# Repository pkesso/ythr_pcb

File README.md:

# PCBs — THR pedalboard

Hardware spec for the JLCPCB build of the control surface. The prototype it
replaces is described in the firmware repository (`feather/doc/wiring.md`); pin
assignments and the 7-segment bit order stay as there, so the firmware does not
change.

## Setup

KiCad 10 (`kicad-cli`) and Python 3 with the packages in `requirements.txt`:

```bash
python -m venv .venv
.venv/Scripts/pip install -r requirements.txt
.venv/Scripts/python effect/gen_effect.py                      # one board
.venv/Scripts/python -m unittest discover -s tests -t tests    # all tests
```

How the boards are generated and tested: [common/README.md](common/README.md).

## Boards

| Dir | Board | MCP23017 | Size (max) | Mask colour |
|-----|-------|----------|------------|-------------|
| `main/` | Main: Main 1 + Main 2 + 7-seg + Feather + bus hub | 0x20, 0x21 | 180 × 110 mm | green |
| `gain-compressor/` | Gate + Compressor (Rev0: hot-swap I²C buffer, VCC ferrite, debounced Q27 push buttons on the board, RJ45 with LEDs) | 0x22 | 50 × 104 mm (template Type_Z-76_Z-77) | yellow |
| `effect/` | Effect (Rev0: Q27 push buttons on the board, RJ45 with LEDs, hot-swap I²C buffer, VCC ferrite) | 0x23 | 50 × 104 mm (template Type_Z-76_Z-77) | purple |
| `echo/` | Echo | 0x24 | 50 × 65 mm | white (black silk) |
| `rever/` | Reverb (Rev0: as Effect) | 0x25 | 50 × 104 mm (template Type_Z-76_Z-77) | blue |
| `presets/` | Presets | 0x26 | 200 × 50 mm | black |

Develop (0x27) gets no PCB.

`common/` is not a board: it holds the generator scripts and the shared KiCad libraries
(see [common/README.md](common/README.md)); `tools/` holds the KiCad helper scripts.

## Mechanics

- Panel: 2 mm. The board hangs on the EC11 bushings (panel rests on the bushing
  shoulder, held by the M7 nuts) — no standoffs.
- Board-to-panel gap = EC11 body height = **6 mm**. Anything taller than 6 mm
  goes on the **bottom side** (Feather, RJ45) or through the panel (the
  7-segment digits, 8 mm: their faces reach the panel window).
- Footswitches and bezel lamps mount to the panel only and are wired to the
  board; they do not overlap the board.
- Main: the Feather's USB-A towards the **top** wall, the 6× RJ45 on the
  **bottom** wall. No USB-C on the board (the Feather headers carry no USB data):
  power and flashing through the Feather's own USB-C.
- Pedal "front" = the far (top) edge, away from the foot: RJ45 there.

## Layout

- **Pedals** (50 × 65, top = RJ45 edge): 4 encoders in a square; with 5, the
  5th in the center. **Gate + Comp, Effect, Reverb and Echo: the square is 32 mm** (encoders 32 mm apart
  across and down; the side ones need the version without the push switch to keep clear of the rim). SMD LEDs
  in a row along the bottom edge, ~10 mm below the lower encoders. Bezel lamps and footswitches sit in the panel
  just below the board edge (not over the board).
- **Main** (180 × 110, centre line x = 90): 5 encoders in the lower row (Gain,
  Master, Bass, Mid, Treble) on a 30 mm pitch, 25 mm above the bottom edge, the
  middle one on the centre line; 4 in the upper row, 25 mm higher, offset by
  15 mm (Amp, Cab, Guitar, Audio). 7-seg top centre (y = 25). Flavor toggle top
  left (40, 35) with its 3 LEDs on a 25 mm radius: blue (Boutique) straight
  above, green (Modern) and orange (Classic) 30° to the left / right. 4 battery
  LEDs in a row top right (x = 140…170, y = 22). Feather (bottom side) right of
  the display, 6 RJ45 along the bottom edge, 3 on each side of the centre.

## MCP23017 block (per chip)

Based on Adafruit #5346.

- MCP23017-E/SS, **SSOP-28** (LCSC C506653).
- 0.1 µF at VDD.
- Address: three **3-pad solder jumpers** (SolderJumper-3 Bridged12), one per bit, pad 2 = Ax. Pad 1 is
  bridged at the factory and goes to this board's level of the bit, pad 3 to the other rail: to change a bit,
  cut the 1–2 bridge and solder 2–3. On every board the left pad is GND (0) and the right pad VCC (1):
  a jumper for a 1 is placed rotated by 180°, so the factory bridge sits on the side of the bit's value.
  `0 1` is printed above the column, `A0`–`A2` beside each jumper. No pull-downs needed.
- 10k pull-up on RESET.
- INTA + INTB wired together (firmware: `IOCON.MIRROR=1, ODR=1`) → bus INT line.
- No power LED.
- I²C pull-ups 2×10k behind a solder jumper, **open by default** (the bus
  pull-ups live on Main).

## Encoder (EC11)

- **Requirement (all boards): 20 pulses per turn, knurled "plum handle" shaft** (serrated, for push-on
  knobs). The PEC11R-4015F-S0024 on the boards today (24 pulses, D-shaft) does not meet it: the encoder is
  to be replaced when the boards are regenerated. **The push switch is not needed**: encoders with it are allowed,
  without it as well (Effect uses PEC11R-4015F-N0024, whose missing switch pins let its side encoders sit closer to
  the edge).
- EC11 with push switch (Bourns PEC11R-4015F-S0024), **15 mm D-shaft**, on the board. The push switch is
  not connected, except on Echo: pushing TIME is a second TAP (switch in parallel with the TAP button).
- Pinout A–C–B (C = common → GND); mounting lugs → GND.
- Per channel (A and B): 10k pull-up to 3.3 V → 10k series → 10 nF to GND at
  the MCP pin (prototype encoder module circuit).

## Footswitch (PBS-24, 12 mm)

- Panel-mounted, wired. On the board: 2 solder holes (GPIO, GND), 2.54 mm
  pitch, ~1.0 mm drill, silkscreen label, near the board edge.
- No filter — direct to the MCP GPIO (internal pull-up + firmware debounce),
  as in the prototype.
- Same 2-hole wiring for the small Echo **tap** button.

## Flavor toggle (Main)

- Momentary toggle **(ON)-OFF-(ON)**, panel-mounted, wired: 3 solder holes
  (GPA0 = prev, GND, GPB0 = next) below an **18 mm hole** in the board for the
  toggle's body (it does not fit in the 6 mm gap).

## Indicator

- External bezel lamp (6 mm panel hole, "3–6 V", built-in resistor): 2 solder
  holes (`+` = GPIO, `−` = GND), no resistor on the board.
- In parallel: **SMD LED 0603, red (JLC basic)** + 470 Ω, in series with a
  solder jumper **open by default** (close it for bench use / clear enclosure).
- Main: **SMD LEDs only** (no lamp pads, no jumper), resistor straight from the
  MCP pin: flavor blue 0603 (extended) and green 0805 (basic) with 100 Ω (higher
  forward voltage), orange 0603 (extended) with 470 Ω; battery LEDs red 0603 +
  470 Ω. Names printed above the LEDs.

## 7-segment display (Main, via Main 2 = 0x21)

- Two single-digit **0.56"** displays (digit body 12.6 × 19 mm), **common
  anode**, **red FJ5161BH** (LCSC C8092, THT, 8 mm tall: the face reaches the
  panel window). Orange / yellow ones with this pinout are not stocked by JLC;
  any 5161BS-type digit fits the same footprint (hand-soldered, then without
  the LCSC number).
- 2 × 74HC595D (basic, one per digit, static drive) + 16 × 470 Ω.
- Signals: GPB6 = SDI, GPA6 = SCLK, GPB7 = LOAD. Bit order as in the
  prototype (WHMXE-595-2): 16-bit word, MSB first; low byte = left digit,
  bit0 = a … bit7 = dp; segment lit = 0.

## Main board

- 2 × MCP23017 (0x20 Main 1, 0x21 Main 2), 9 × EC11, flavor toggle,
  7 indicators, 7-seg.
- **Feather RP2040 USB Host (#5723)** on female headers (1×16 + 1×12), bottom
  side, USB-A towards the top wall. JP1.13 GND, JP1.14–15 3V3, JP3.11 SCL,
  JP3.12 SDA, JP3.10 (D5) INT; nothing else connected.
- **6 × RJ45** (5 pedals + 1 spare), star topology, bottom side, plug openings
  flush with the bottom edge. TVS (SRV05-4) on SCL / SDA / INT / VCC at each jack.
- Feather sockets and RJ45 are **soldered by hand** (holes only, not in the
  BOM): JLC Economic PCBA places parts on one side only.
- Bus pull-ups (the only ones on the bus): SCL / SDA 2.2k, INT 10k → 3.3 V;
  INT → Feather D5 (not used by the firmware yet; it will need `IOCON.ODR=1`
  on every chip, since all INT outputs share the line).
- Main 1 left of the Amp encoder, Main 2 on the top side between the Feather's
  socket rows (the Feather is underneath).
- Bus power: 3.3 V from the Feather regulator.
- Bluetooth: external CSR8510 dongle (not integrated).

## Pedal boards

- 1 × MCP23017 + controls (see the per-pedal tables in wiring.md) + 1 × RJ45
  (bottom side, front edge) + 10 µF bulk at the jack.

## Bus cable (8P8C)

| Wire | Signal |
|------|--------|
| White-Orange | GND |
| Orange | SCL |
| White-Green | GND |
| Blue | SDA |
| White-Blue | GND |
| Green | VCC 3.3 V |
| White-Brown | GND (return for INT) |
| Brown | **INT** (open-drain, active low) |

## Parts / cost notes

- Prefer JLC **basic** parts; each **extended** part costs +$3 per design.
- SMD LED: red, basic — no extended fee.
- Final LCSC part numbers and prices — at the BOM stage.

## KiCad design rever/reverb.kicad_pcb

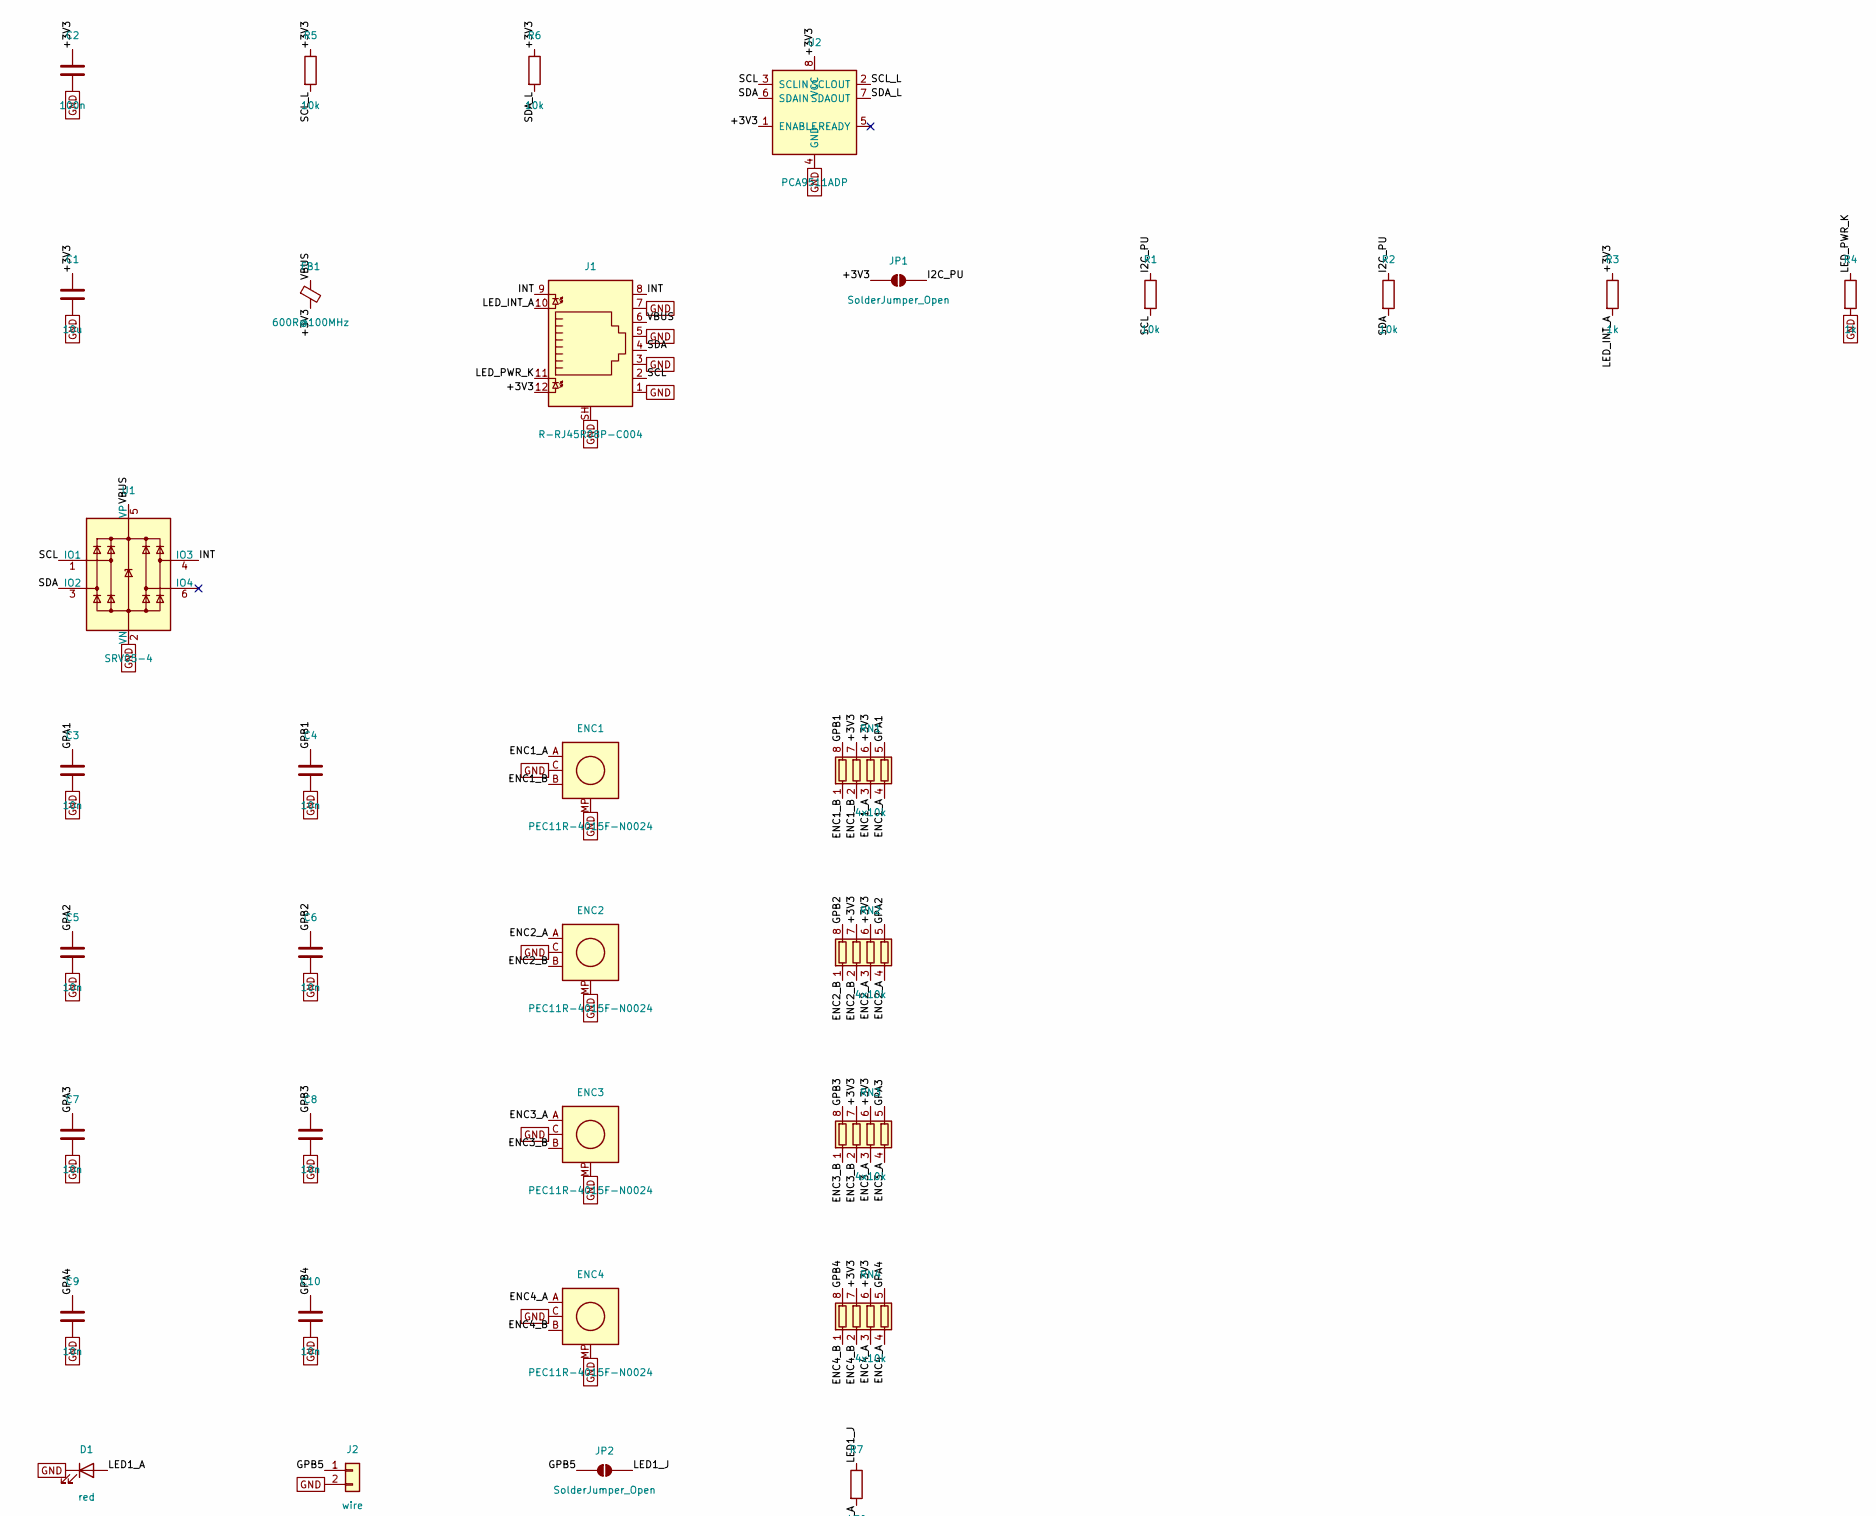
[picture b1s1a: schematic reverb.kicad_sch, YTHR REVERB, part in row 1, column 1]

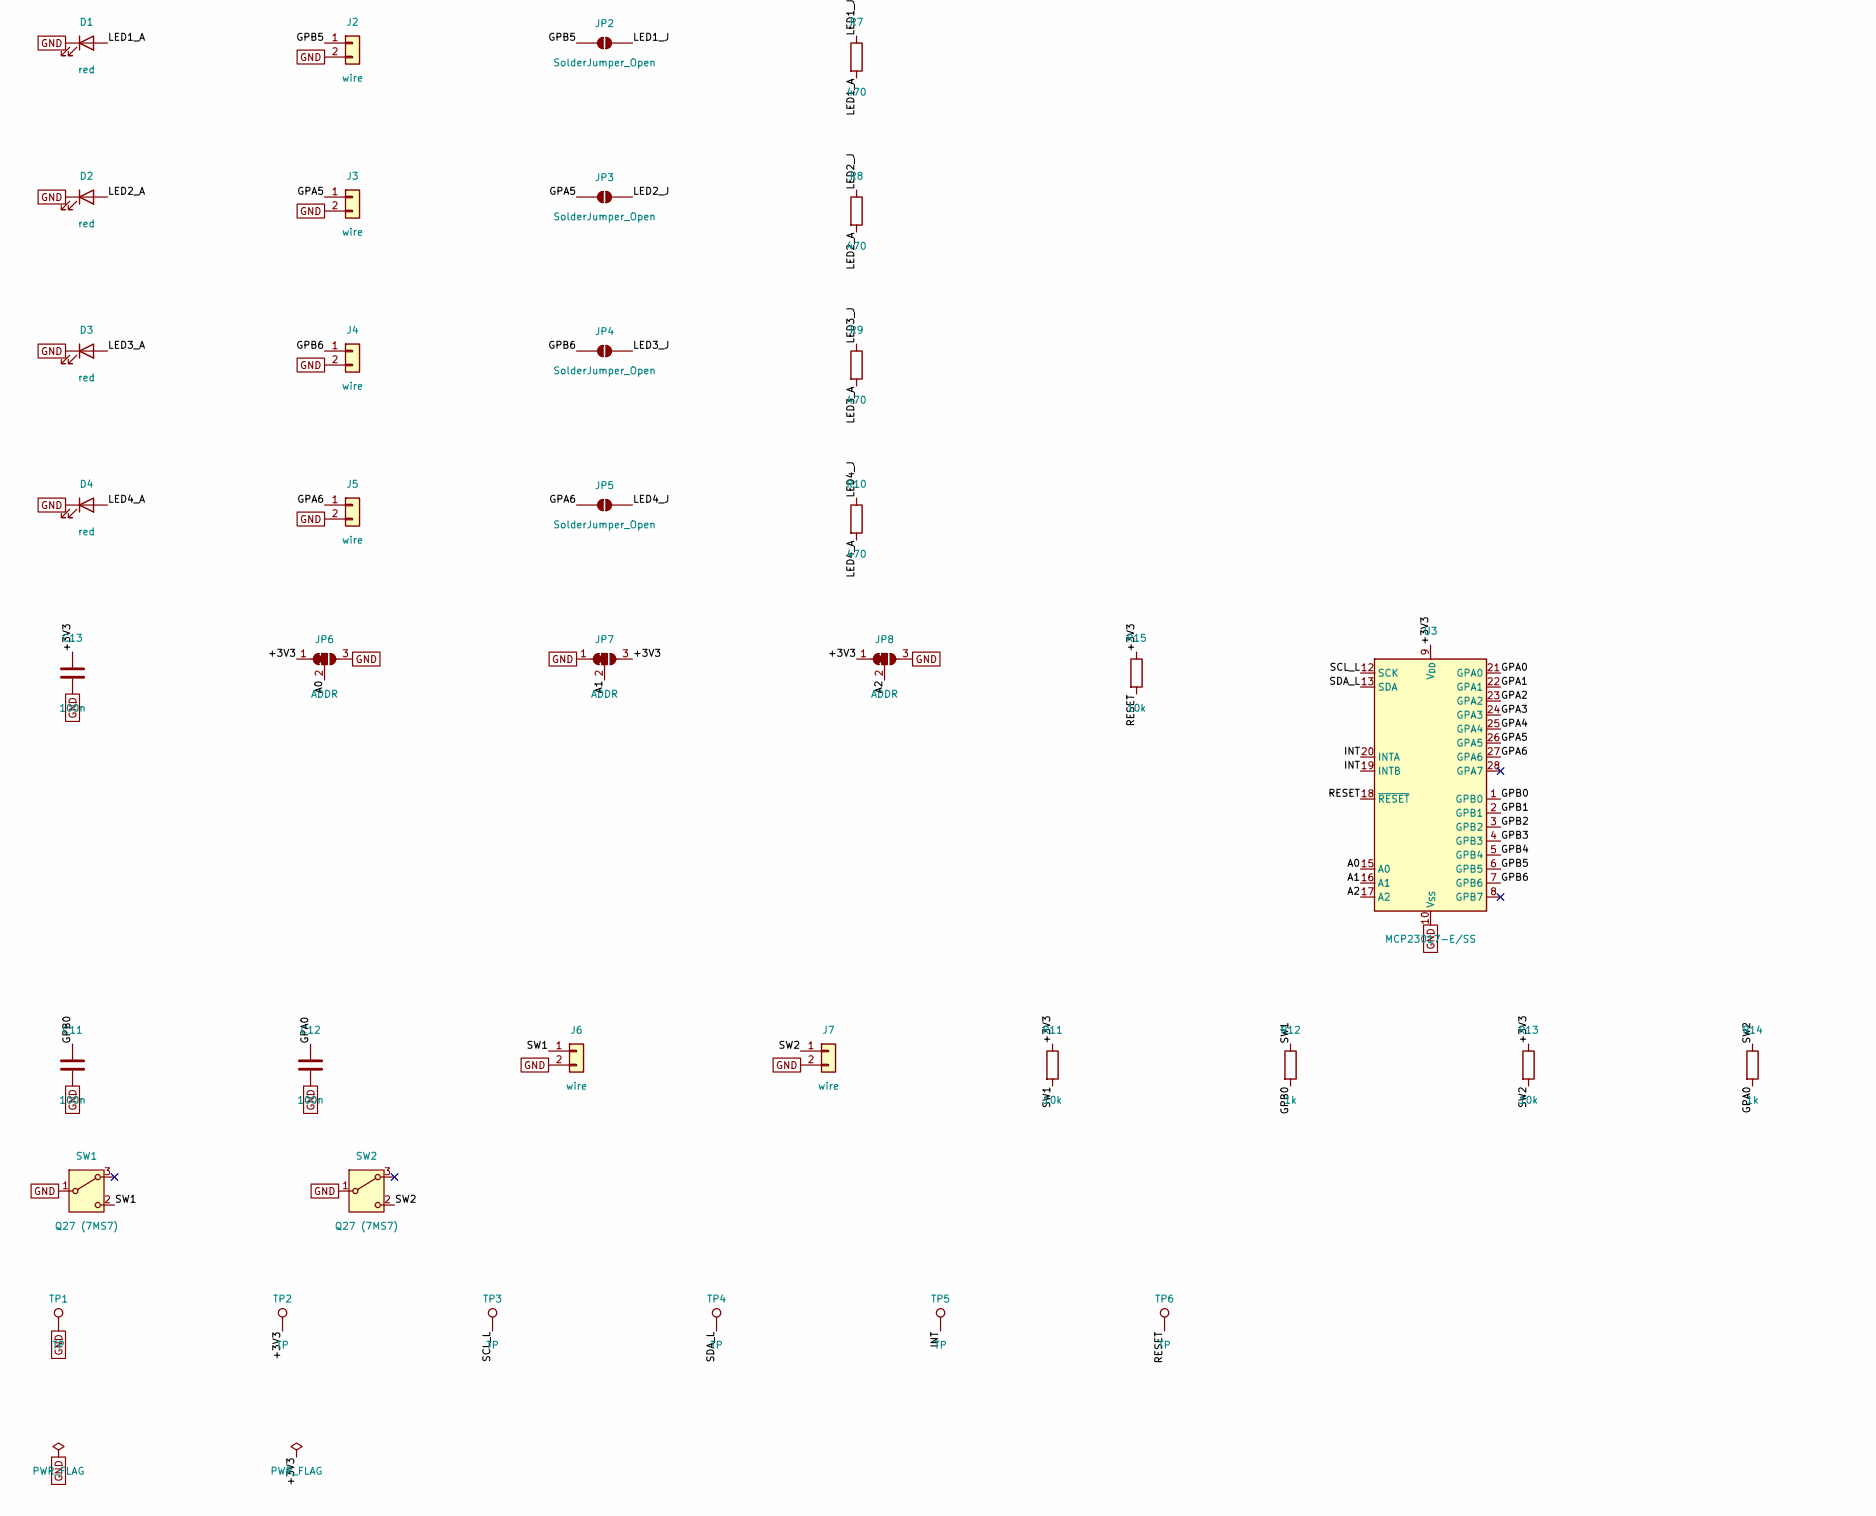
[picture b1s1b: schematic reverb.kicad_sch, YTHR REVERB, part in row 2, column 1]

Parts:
C1: 10u; C_0805_2012Metric; LCSC C15850
C2, C11, C12, C13: 100n; C_0603_1608Metric; LCSC C14663
C3, C4, C5, C6, C7, C8, C9, C10: 10n; C_0603_1608Metric; LCSC C57112
D1, D2, D3, D4: red; LED_0603_1608Metric; LCSC C2286
ENC1, ENC2, ENC3, ENC4: PEC11R-4015F-N0024; RotaryEncoder_Bourns_Vertical_PEC11R-4xxxF-Nxxxx; LCSC C22402500
FB1: 600R@100MHz; L_0603_1608Metric; LCSC C1002
J1: R-RJ45R08P-C004; RJ45_Ckmtw_R-RJ45R08P-C004_Horizontal
J2, J3, J4, J5, J6, J7: wire; WirePads_1x02_P2.54mm_Drill1.0mm
JP1, JP2, JP3, JP4, JP5: SolderJumper_Open; SolderJumper-2_P1.3mm_Open_RoundedPad1.0x1.5mm
JP6, JP7, JP8: ADDR; SolderJumper-3_P1.3mm_Bridged12_RoundedPad1.0x1.5mm
R1, R2, R5, R6, R11, R13, R15: 10k; R_0603_1608Metric; LCSC C25804
R3, R4, R12, R14: 1k; R_0603_1608Metric; LCSC C21190
R7, R8, R9, R10: 470; R_0603_1608Metric; LCSC C23179
RN1, RN2, RN3, RN4: 4x10k; R_Array_Convex_4x0603; LCSC C29718
SW1, SW2: Q27 (7MS7); PushButton_Q27_15-32UNS_SPDT_SolderLug
TP1, TP2, TP3, TP4, TP5, TP6: TP; TestPoint_Pad_D1.5mm
U1: SRV05-4; SOT-23-6; LCSC C558418
U2: PCA9511ADP; TSSOP-8_4.4x3mm_P0.65mm; LCSC C545194
U3: MCP23017-E/SS; SSOP-28_5.3x10.2mm_P0.65mm; LCSC C506653

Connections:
/+3V3: C1.1, C2.1, C13.1, FB1.2, J1.12, JP1.1 (A), JP6.1 (A), JP7.3 (B), JP8.1 (A), R3.1, R5.1, R6.1, R11.1, R13.1, R15.1, RN1.6 (R3.2), RN1.7 (R2.2), RN2.6 (R3.2), RN2.7 (R2.2), RN3.6 (R3.2), RN3.7 (R2.2), RN4.6 (R3.2), RN4.7 (R2.2), TP2.1, U2.1 (ENABLE), U2.8 (VCC), U3.9 (V_{DD})
/A0: JP6.2 (C), U3.15 (A0)
/A1: JP7.2 (C), U3.16 (A1)
/A2: JP8.2 (C), U3.17 (A2)
/ENC1_A: ENC1.A, RN1.3 (R3.1), RN1.4 (R4.1)
/ENC1_B: ENC1.B, RN1.1 (R1.1), RN1.2 (R2.1)
/ENC2_A: ENC2.A, RN2.3 (R3.1), RN2.4 (R4.1)
/ENC2_B: ENC2.B, RN2.1 (R1.1), RN2.2 (R2.1)
/ENC3_A: ENC3.A, RN3.3 (R3.1), RN3.4 (R4.1)
/ENC3_B: ENC3.B, RN3.1 (R1.1), RN3.2 (R2.1)
/ENC4_A: ENC4.A, RN4.3 (R3.1), RN4.4 (R4.1)
/ENC4_B: ENC4.B, RN4.1 (R1.1), RN4.2 (R2.1)
/GPA0: C12.1, R14.2, U3.21 (GPA0)
/GPA1: C3.1, RN1.5 (R4.2), U3.22 (GPA1)
/GPA2: C5.1, RN2.5 (R4.2), U3.23 (GPA2)
/GPA3: C7.1, RN3.5 (R4.2), U3.24 (GPA3)
/GPA4: C9.1, RN4.5 (R4.2), U3.25 (GPA4)
/GPA5: J3.1, JP3.1 (A), U3.26 (GPA5)
/GPA6: J5.1, JP5.1 (A), U3.27 (GPA6)
/GPB0: C11.1, R12.2, U3.1 (GPB0)
/GPB1: C4.1, RN1.8 (R1.2), U3.2 (GPB1)
/GPB2: C6.1, RN2.8 (R1.2), U3.3 (GPB2)
/GPB3: C8.1, RN3.8 (R1.2), U3.4 (GPB3)
/GPB4: C10.1, RN4.8 (R1.2), U3.5 (GPB4)
/GPB5: J2.1, JP2.1 (A), U3.6 (GPB5)
/GPB6: J4.1, JP4.1 (A), U3.7 (GPB6)
/I2C_PU: JP1.2 (B), R1.1, R2.1
/INT: J1.8, J1.9, TP5.1, U1.4 (IO3), U3.19 (INTB), U3.20 (INTA)
/LED1_A: D1.2 (A), R7.2
/LED1_J: JP2.2 (B), R7.1
/LED2_A: D2.2 (A), R8.2
/LED2_J: JP3.2 (B), R8.1
/LED3_A: D3.2 (A), R9.2
/LED3_J: JP4.2 (B), R9.1
/LED4_A: D4.2 (A), R10.2
/LED4_J: JP5.2 (B), R10.1
/LED_INT_A: J1.10, R3.2
/LED_PWR_K: J1.11, R4.1
/RESET: R15.2, TP6.1, U3.18 (~RESET)
/SCL: J1.2, R1.2, U1.1 (IO1), U2.3 (SCLIN)
/SCL_L: R5.2, TP3.1, U2.2 (SCLOUT), U3.12 (SCK)
/SDA: J1.4, R2.2, U1.3 (IO2), U2.6 (SDAIN)
/SDA_L: R6.2, TP4.1, U2.7 (SDAOUT), U3.13 (SDA)
/SW1: J6.1, R11.2, R12.1, SW1.2 (C)
/SW2: J7.1, R13.2, R14.1, SW2.2 (C)
/VBUS: FB1.1, J1.6, U1.5 (VP)
GND: C1.2, C2.2, C3.2, C4.2, C5.2, C6.2, C7.2, C8.2, C9.2, C10.2, C11.2, C12.2, C13.2, D1.1 (K), D2.1 (K), D3.1 (K), D4.1 (K), ENC1.C, ENC1.MP, ENC2.C, ENC2.MP, ENC3.C, ENC3.MP, ENC4.C, ENC4.MP, J1.1, J1.3, J1.5, J1.7, J1.SH, J2.2, J3.2, J4.2, J5.2, J6.2, J7.2, JP6.3 (B), JP7.1 (A), JP8.3 (B), R4.2, SW1.1 (B), SW2.1 (B), TP1.1, U1.2 (VN), U2.4 (GND), U3.10 (V_{SS})

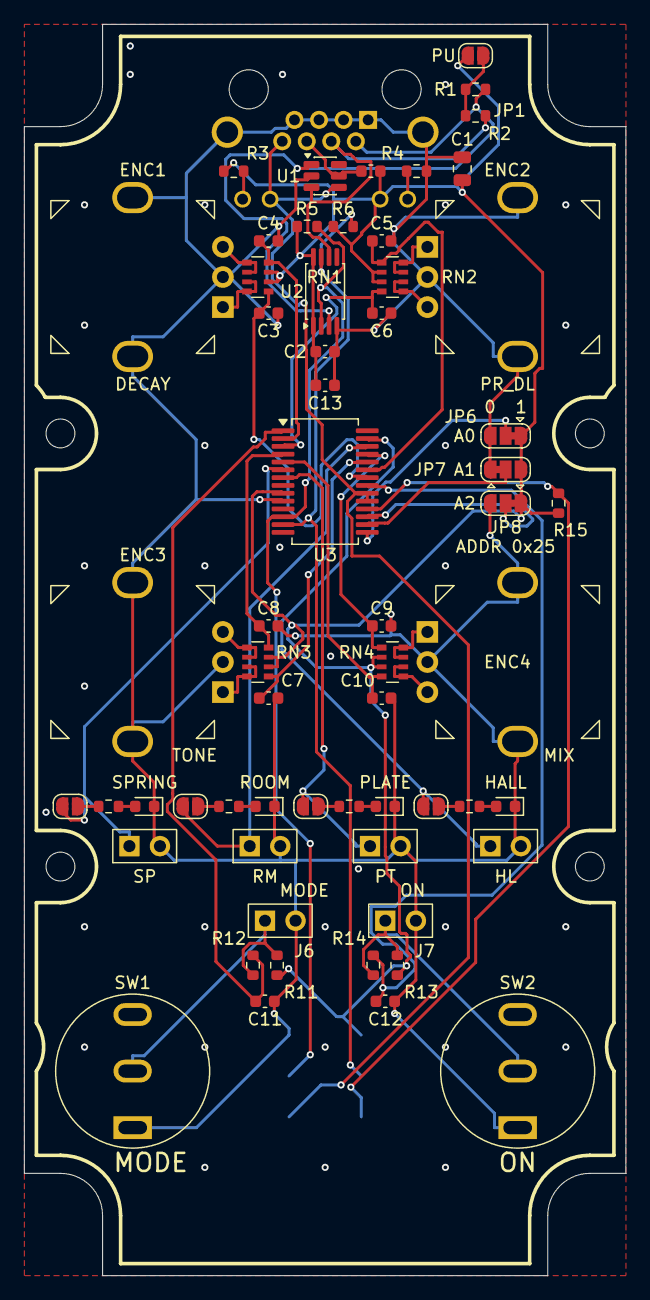
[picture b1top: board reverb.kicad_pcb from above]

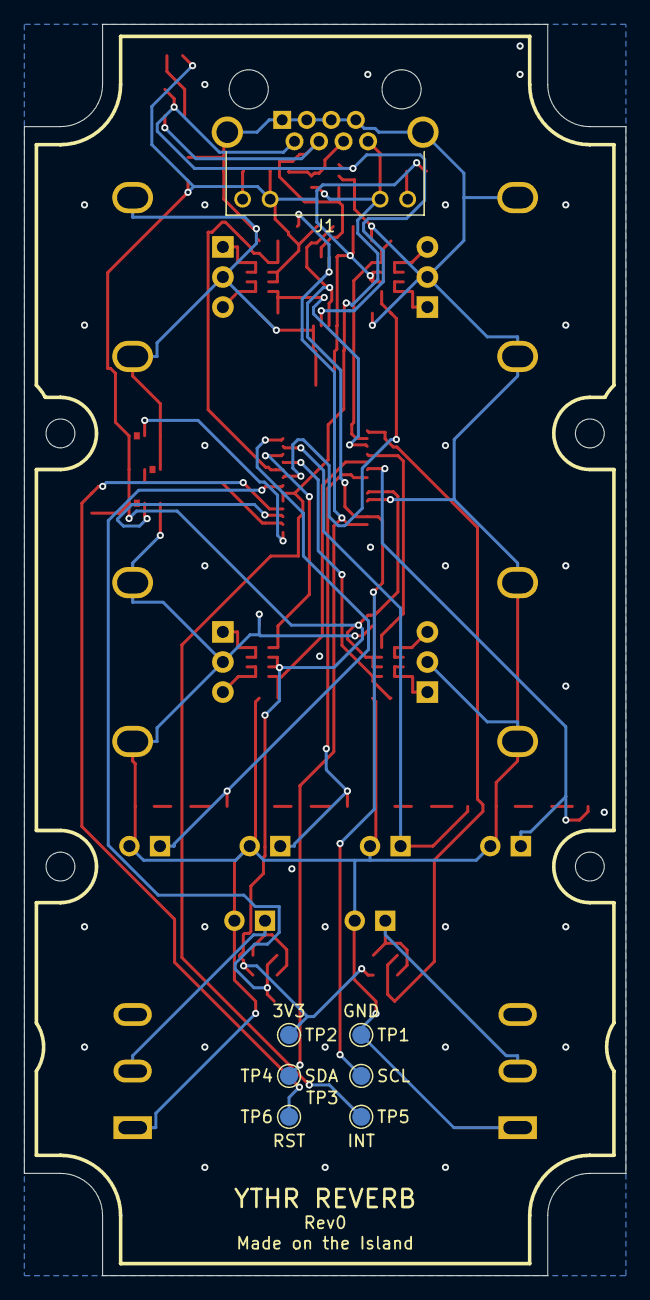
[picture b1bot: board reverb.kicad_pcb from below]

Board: 2 copper layers, 50.0 x 104.0 mm, 67 parts (7 on the bottom side), 47 nets.

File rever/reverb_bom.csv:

Comment,Designator,Footprint,LCSC Part #
10u,C1,C_0805_2012Metric,C15850
100n,"C2,C11,C12,C13",C_0603_1608Metric,C14663
10n,"C3,C4,C5,C6,C7,C8,C9,C10",C_0603_1608Metric,C57112
red,"D1,D2,D3,D4",LED_0603_1608Metric,C2286
PEC11R-4015F-N0024,"ENC1,ENC2,ENC3,ENC4",RotaryEncoder_Bourns_Vertical_PEC11R-4xxxF-Nxxxx,C22402500
600R@100MHz,FB1,L_0603_1608Metric,C1002
10k,"R1,R2,R5,R6,R11,R13,R15",R_0603_1608Metric,C25804
1k,"R3,R4,R12,R14",R_0603_1608Metric,C21190
470,"R7,R8,R9,R10",R_0603_1608Metric,C23179
4x10k,"RN1,RN2,RN3,RN4",R_Array_Convex_4x0603,C29718
SRV05-4,U1,SOT-23-6,C558418
PCA9511ADP,U2,TSSOP-8_4.4x3mm_P0.65mm,C545194
MCP23017-E/SS,U3,SSOP-28_5.3x10.2mm_P0.65mm,C506653

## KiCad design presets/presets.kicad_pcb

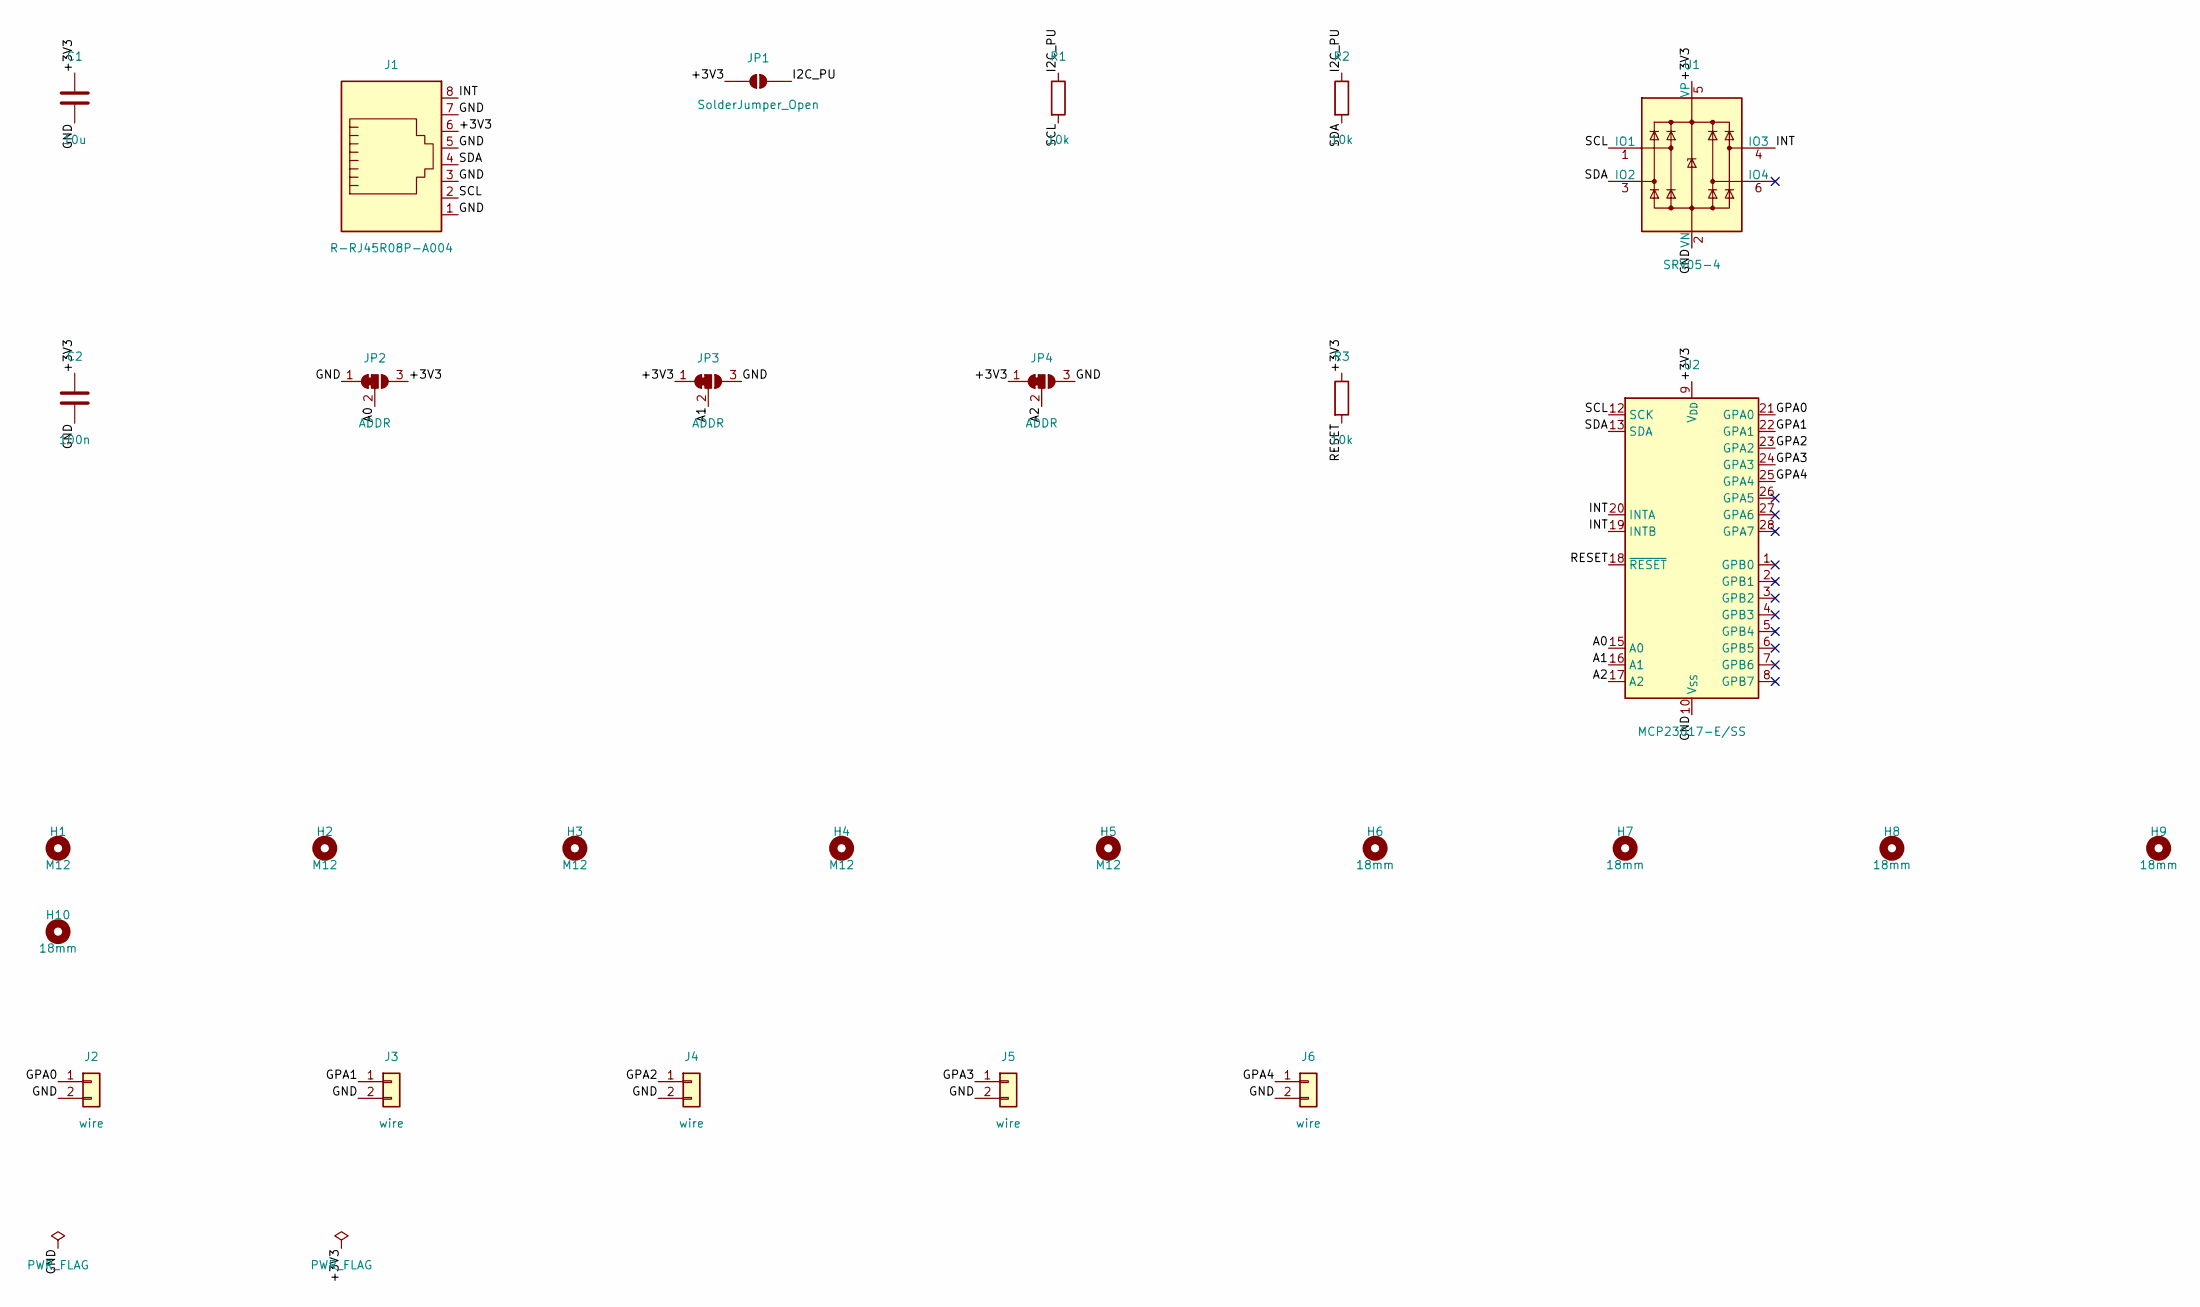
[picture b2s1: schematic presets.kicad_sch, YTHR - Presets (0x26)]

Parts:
C1: 10u; C_0805_2012Metric; LCSC C15850
C2: 100n; C_0603_1608Metric; LCSC C14663
H1, H2, H3, H4, H5: M12; Hole_M12_Footswitch
H6, H7, H8, H9, H10: 18mm; Hole_18mm_NoHead
J1: R-RJ45R08P-A004; RJ45_Ckmtw_R-RJ45R08P-A004_Horizontal; LCSC C385834
J2, J3, J4, J5, J6: wire; WirePads_1x02_P2.54mm_Drill1.0mm
JP1: SolderJumper_Open; SolderJumper-2_P1.3mm_Open_RoundedPad1.0x1.5mm
JP2, JP3, JP4: ADDR; SolderJumper-3_P1.3mm_Bridged12_RoundedPad1.0x1.5mm
R1, R2, R3: 10k; R_0603_1608Metric; LCSC C25804
U1: SRV05-4; SOT-23-6; LCSC C558418
U2: MCP23017-E/SS; SSOP-28_5.3x10.2mm_P0.65mm; LCSC C506653

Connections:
/+3V3: C1.1, C2.1, J1.6, JP1.1 (A), JP2.3 (B), JP3.1 (A), JP4.1 (A), R3.1, U1.5 (VP), U2.9 (V_{DD})
/A0: JP2.2 (C), U2.15 (A0)
/A1: JP3.2 (C), U2.16 (A1)
/A2: JP4.2 (C), U2.17 (A2)
/GND: C1.2, C2.2, J1.1, J1.3, J1.5, J1.7, J2.2, J3.2, J4.2, J5.2, J6.2, JP2.1 (A), JP3.3 (B), JP4.3 (B), U1.2 (VN), U2.10 (V_{SS})
/GPA0: J2.1, U2.21 (GPA0)
/GPA1: J3.1, U2.22 (GPA1)
/GPA2: J4.1, U2.23 (GPA2)
/GPA3: J5.1, U2.24 (GPA3)
/GPA4: J6.1, U2.25 (GPA4)
/I2C_PU: JP1.2 (B), R1.1, R2.1
/INT: J1.8, U1.4 (IO3), U2.19 (INTB), U2.20 (INTA)
/RESET: R3.2, U2.18 (~RESET)
/SCL: J1.2, R1.2, U1.1 (IO1), U2.12 (SCK)
/SDA: J1.4, R2.2, U1.3 (IO2), U2.13 (SDA)

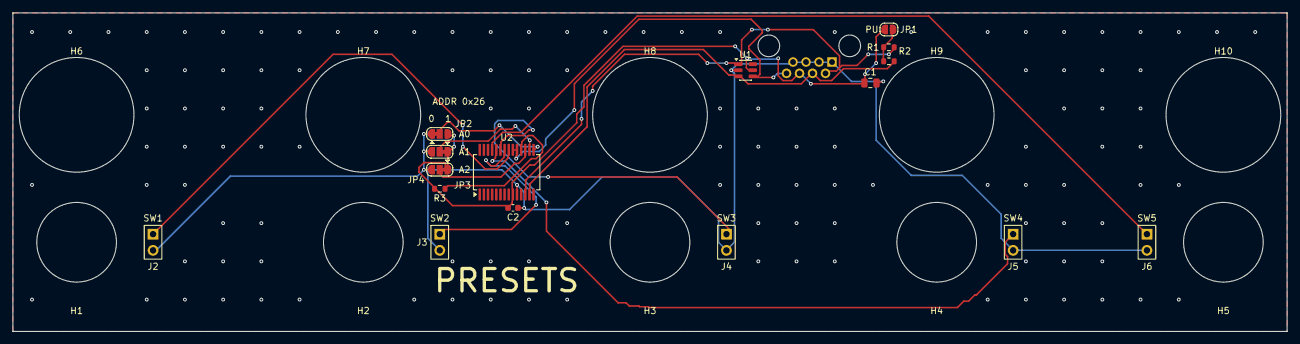
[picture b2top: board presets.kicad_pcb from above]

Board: 2 copper layers, 200.0 x 50.0 mm, 27 parts (1 on the bottom side), 15 nets.

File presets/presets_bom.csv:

Comment,Designator,Footprint,LCSC Part #
10u,C1,C_0805_2012Metric,C15850
100n,C2,C_0603_1608Metric,C14663
R-RJ45R08P-A004,J1,RJ45_Ckmtw_R-RJ45R08P-A004_Horizontal,C385834
10k,"R1,R2,R3",R_0603_1608Metric,C25804
SRV05-4,U1,SOT-23-6,C558418
MCP23017-E/SS,U2,SSOP-28_5.3x10.2mm_P0.65mm,C506653

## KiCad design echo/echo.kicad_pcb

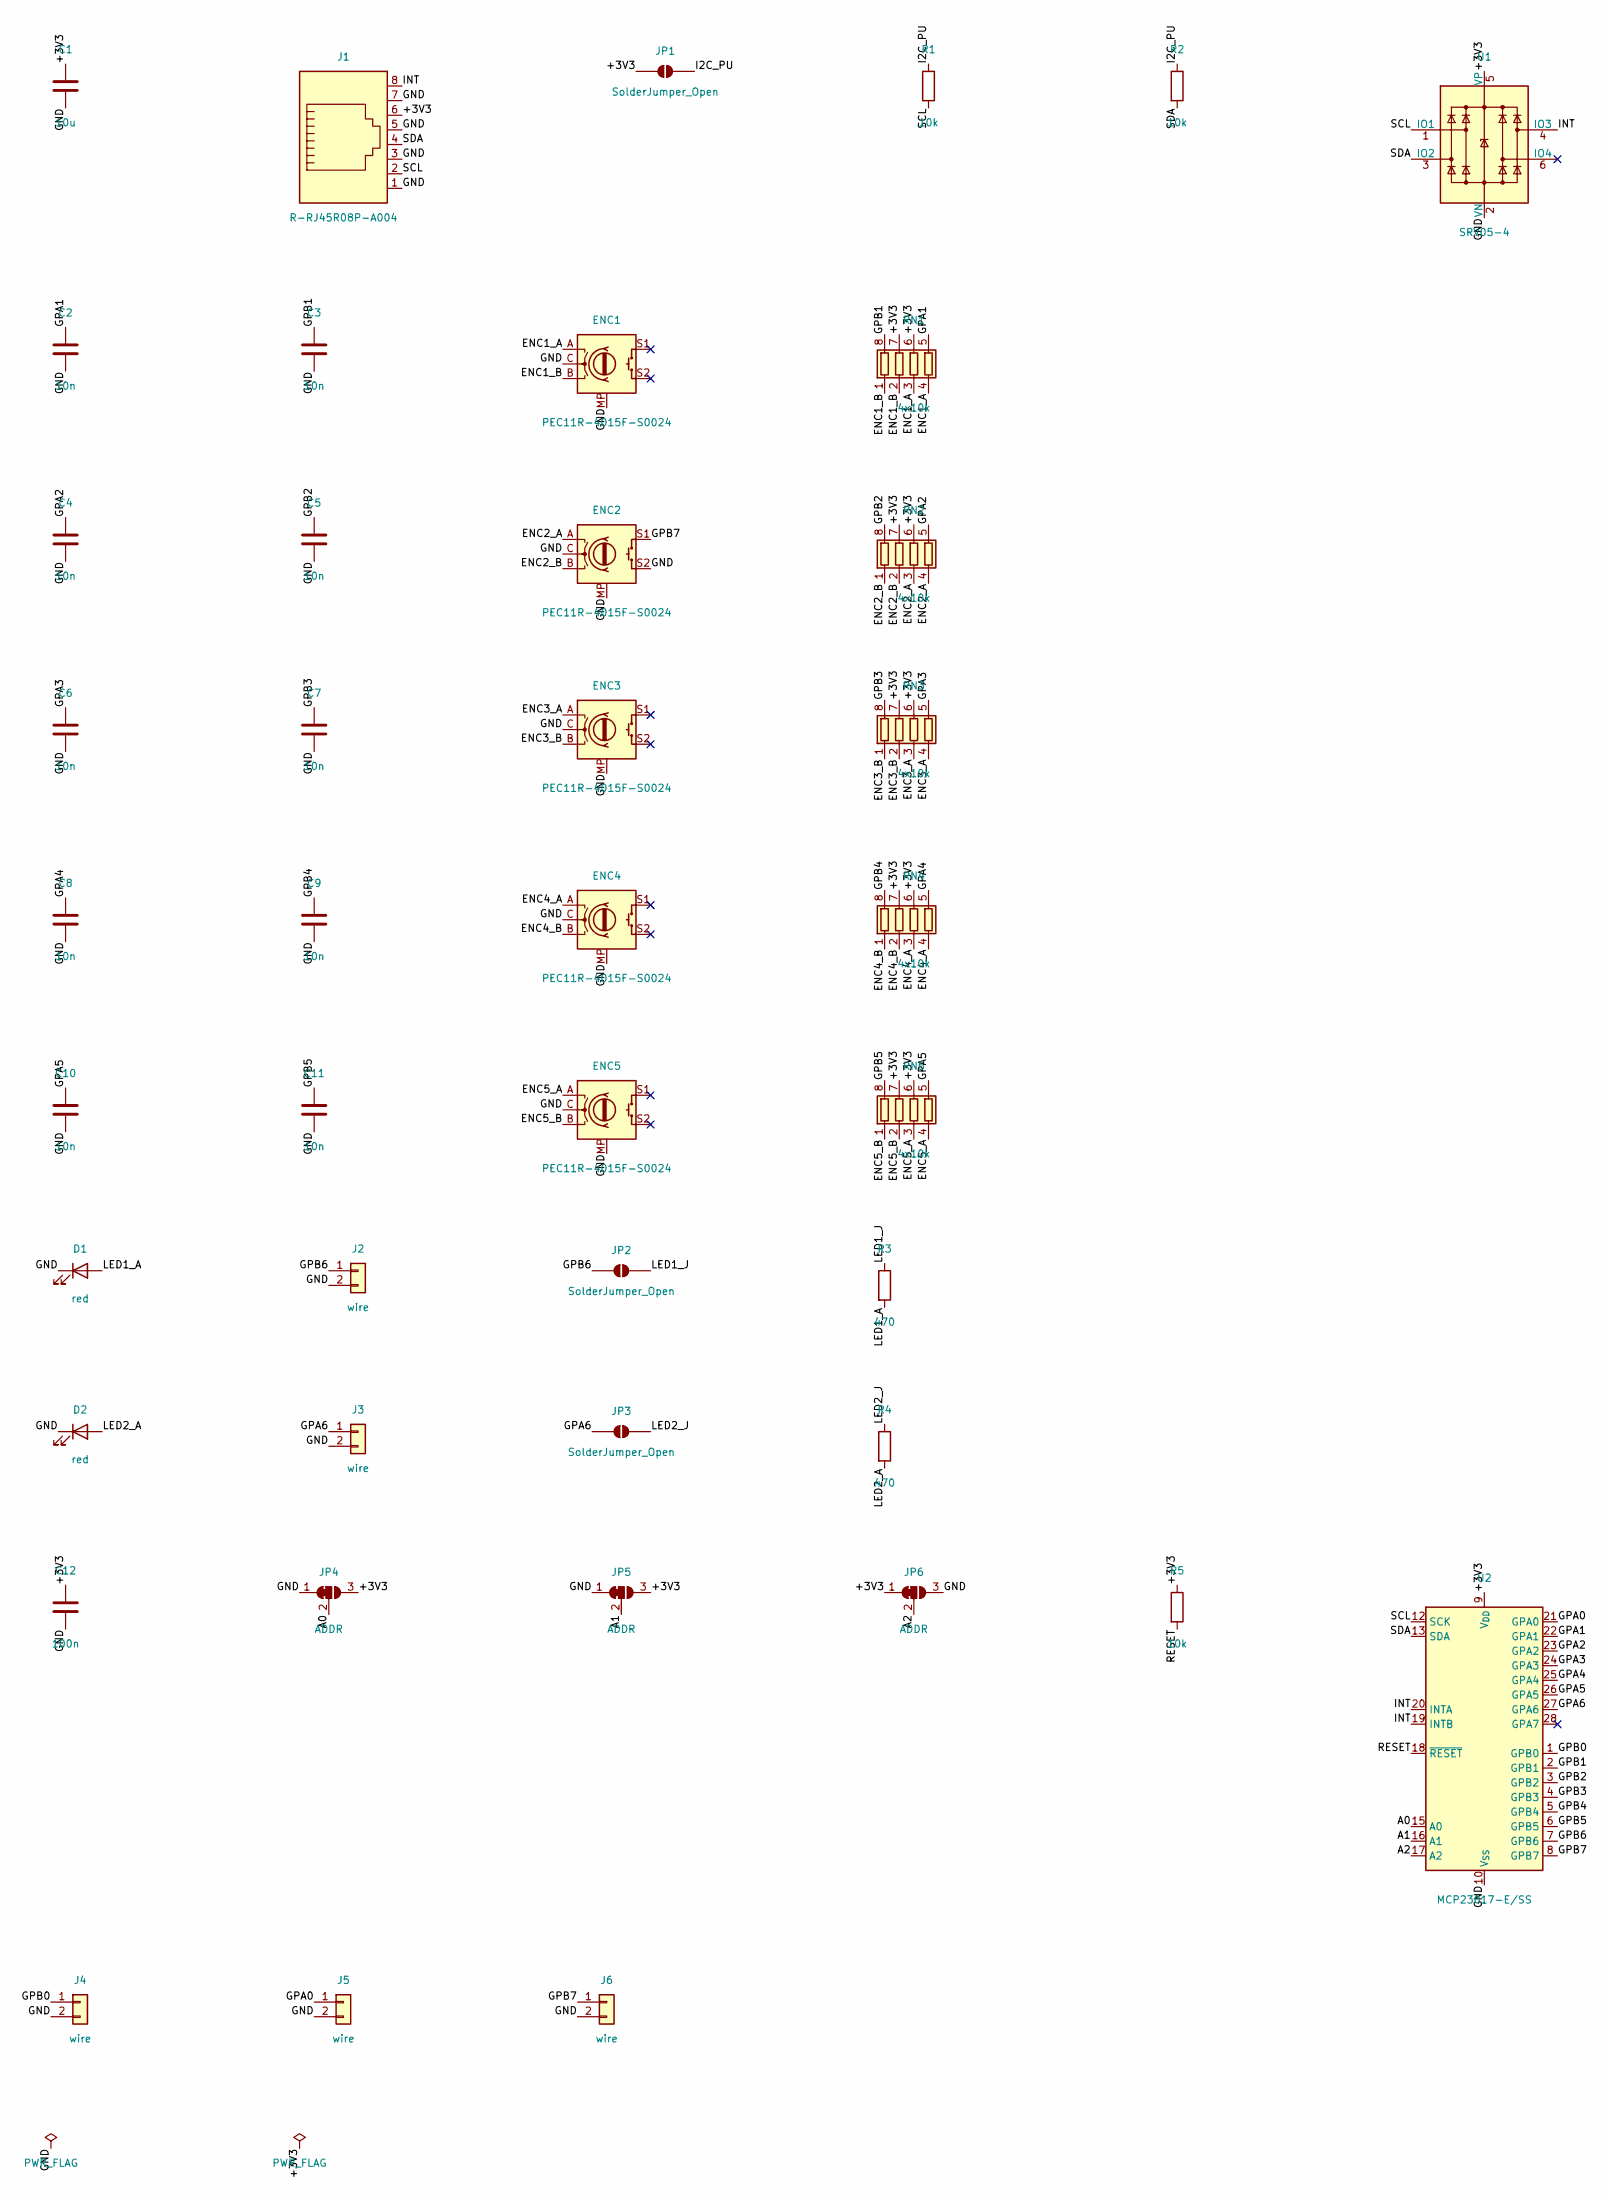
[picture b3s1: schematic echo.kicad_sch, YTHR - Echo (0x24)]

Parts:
C1: 10u; C_0805_2012Metric; LCSC C15850
C2, C3, C4, C5, C6, C7, C8, C9, C10, C11: 10n; C_0603_1608Metric; LCSC C57112
C12: 100n; C_0603_1608Metric; LCSC C14663
D1, D2: red; LED_0603_1608Metric; LCSC C2286
ENC1, ENC2, ENC3, ENC4, ENC5: PEC11R-4015F-S0024; RotaryEncoder_Bourns_Vertical_PEC11R-4xxxF-Sxxxx; LCSC C143789
J1: R-RJ45R08P-A004; RJ45_Ckmtw_R-RJ45R08P-A004_Horizontal; LCSC C385834
J2, J3, J4, J5, J6: wire; WirePads_1x02_P2.54mm_Drill1.0mm
JP1, JP2, JP3: SolderJumper_Open; SolderJumper-2_P1.3mm_Open_RoundedPad1.0x1.5mm
JP4, JP5, JP6: ADDR; SolderJumper-3_P1.3mm_Bridged12_RoundedPad1.0x1.5mm
R1, R2, R5: 10k; R_0603_1608Metric; LCSC C25804
R3, R4: 470; R_0603_1608Metric; LCSC C23179
RN1, RN2, RN3, RN4, RN5: 4x10k; R_Array_Convex_4x0603; LCSC C29718
U1: SRV05-4; SOT-23-6; LCSC C558418
U2: MCP23017-E/SS; SSOP-28_5.3x10.2mm_P0.65mm; LCSC C506653

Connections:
/+3V3: C1.1, C12.1, J1.6, JP1.1 (A), JP4.3 (B), JP5.3 (B), JP6.1 (A), R5.1, RN1.6 (R3.2), RN1.7 (R2.2), RN2.6 (R3.2), RN2.7 (R2.2), RN3.6 (R3.2), RN3.7 (R2.2), RN4.6 (R3.2), RN4.7 (R2.2), RN5.6 (R3.2), RN5.7 (R2.2), U1.5 (VP), U2.9 (V_{DD})
/A0: JP4.2 (C), U2.15 (A0)
/A1: JP5.2 (C), U2.16 (A1)
/A2: JP6.2 (C), U2.17 (A2)
/ENC1_A: ENC1.A, RN1.3 (R3.1), RN1.4 (R4.1)
/ENC1_B: ENC1.B, RN1.1 (R1.1), RN1.2 (R2.1)
/ENC2_A: ENC2.A, RN2.3 (R3.1), RN2.4 (R4.1)
/ENC2_B: ENC2.B, RN2.1 (R1.1), RN2.2 (R2.1)
/ENC3_A: ENC3.A, RN3.3 (R3.1), RN3.4 (R4.1)
/ENC3_B: ENC3.B, RN3.1 (R1.1), RN3.2 (R2.1)
/ENC4_A: ENC4.A, RN4.3 (R3.1), RN4.4 (R4.1)
/ENC4_B: ENC4.B, RN4.1 (R1.1), RN4.2 (R2.1)
/ENC5_A: ENC5.A, RN5.3 (R3.1), RN5.4 (R4.1)
/ENC5_B: ENC5.B, RN5.1 (R1.1), RN5.2 (R2.1)
/GND: C1.2, C2.2, C3.2, C4.2, C5.2, C6.2, C7.2, C8.2, C9.2, C10.2, C11.2, C12.2, D1.1 (K), D2.1 (K), ENC1.C, ENC1.MP, ENC2.C, ENC2.MP, ENC2.S2, ENC3.C, ENC3.MP, ENC4.C, ENC4.MP, ENC5.C, ENC5.MP, J1.1, J1.3, J1.5, J1.7, J2.2, J3.2, J4.2, J5.2, J6.2, JP4.1 (A), JP5.1 (A), JP6.3 (B), U1.2 (VN), U2.10 (V_{SS})
/GPA0: J5.1, U2.21 (GPA0)
/GPA1: C2.1, RN1.5 (R4.2), U2.22 (GPA1)
/GPA2: C4.1, RN2.5 (R4.2), U2.23 (GPA2)
/GPA3: C6.1, RN3.5 (R4.2), U2.24 (GPA3)
/GPA4: C8.1, RN4.5 (R4.2), U2.25 (GPA4)
/GPA5: C10.1, RN5.5 (R4.2), U2.26 (GPA5)
/GPA6: J3.1, JP3.1 (A), U2.27 (GPA6)
/GPB0: J4.1, U2.1 (GPB0)
/GPB1: C3.1, RN1.8 (R1.2), U2.2 (GPB1)
/GPB2: C5.1, RN2.8 (R1.2), U2.3 (GPB2)
/GPB3: C7.1, RN3.8 (R1.2), U2.4 (GPB3)
/GPB4: C9.1, RN4.8 (R1.2), U2.5 (GPB4)
/GPB5: C11.1, RN5.8 (R1.2), U2.6 (GPB5)
/GPB6: J2.1, JP2.1 (A), U2.7 (GPB6)
/GPB7: ENC2.S1, J6.1, U2.8 (GPB7)
/I2C_PU: JP1.2 (B), R1.1, R2.1
/INT: J1.8, U1.4 (IO3), U2.19 (INTB), U2.20 (INTA)
/LED1_A: D1.2 (A), R3.2
/LED1_J: JP2.2 (B), R3.1
/LED2_A: D2.2 (A), R4.2
/LED2_J: JP3.2 (B), R4.1
/RESET: R5.2, U2.18 (~RESET)
/SCL: J1.2, R1.2, U1.1 (IO1), U2.12 (SCK)
/SDA: J1.4, R2.2, U1.3 (IO2), U2.13 (SDA)
